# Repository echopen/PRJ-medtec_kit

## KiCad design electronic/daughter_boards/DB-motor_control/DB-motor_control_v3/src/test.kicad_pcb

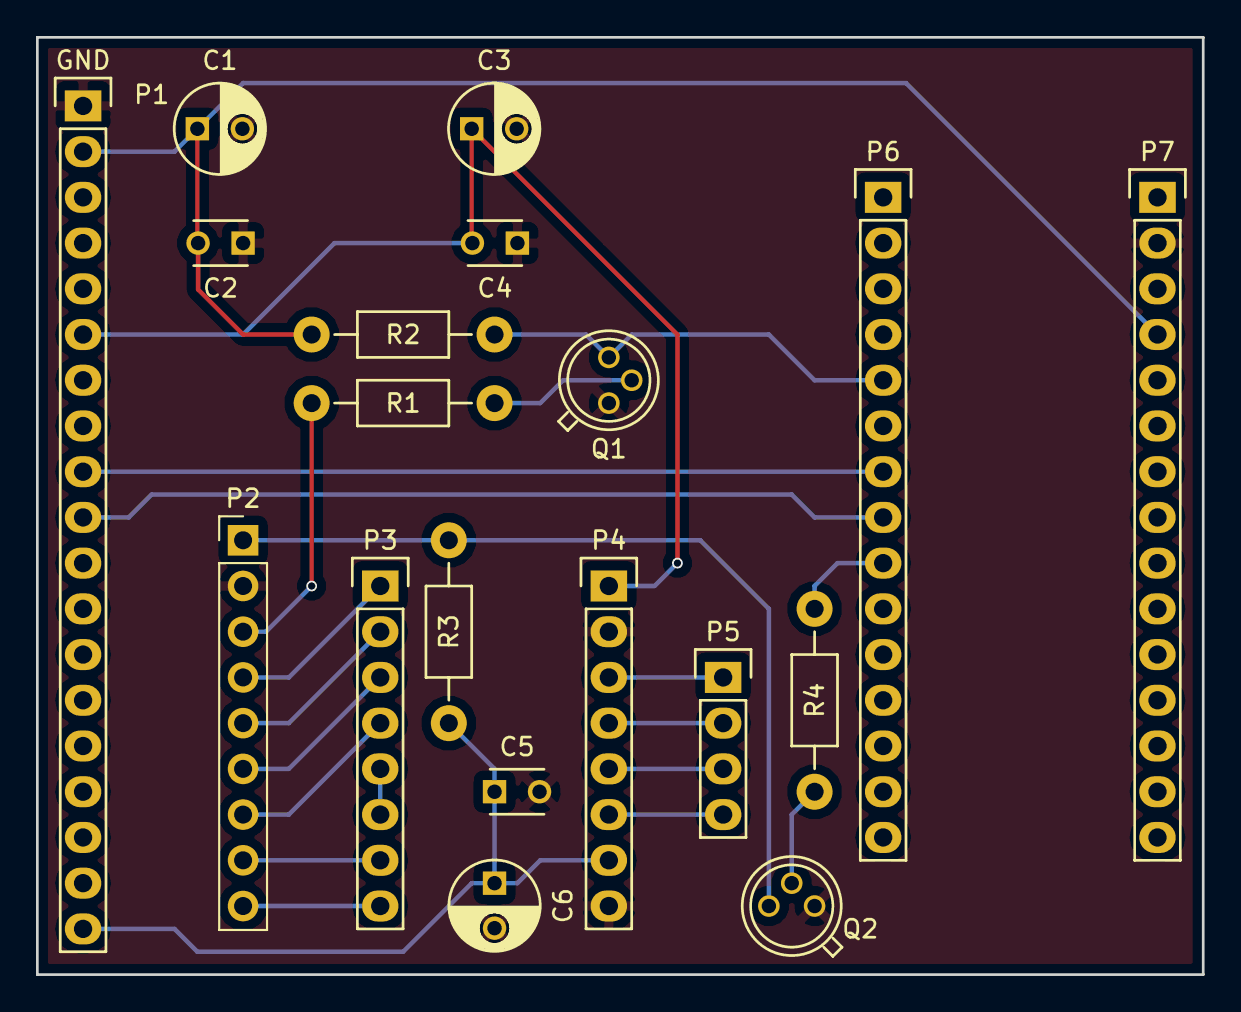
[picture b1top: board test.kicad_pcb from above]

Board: 2 copper layers, 64.8 x 52.1 mm, 19 parts (0 on the bottom side), 23 nets.

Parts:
C1, C6: 10u; CP_small_TH_echopen
C2, C4: 100n; C_small_TH_echopen
C3: 100u; CP_small_TH_echopen
C5: 47n; C_small_TH_echopen
P1: CONN_01X19; Header_pin_angled_1x19
P2: CONN_01X09; Socket_Strip_Straight_1x09_Pitch2.54mm
P3, P4: CONN_01X08; Pin_Header_Straight_1x08
P5: CONN_01X04; Pin_Header_Straight_1x04
P6: CONN_01X15; Socket_Strip_Straight_1x15
P7: CONN_01X15; Pin_Header_Straight_1x15
Q1, Q2: 2N2222; TO-18_TH_common
R1, R4: 680; Resistor_TH_common
R2, R3: 1.5k; Resistor_TH_common

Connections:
GND: C1.2, C2.1, C3.2, C4.1, C5.2, C6.2, P1.1, P2.2, P4.2, P4.8, P7.2, Q1.1, Q2.1
unnamed: C1.1, C2.2, P1.2, P7.4, R2.2
unnamed: C3.1, C4.2, P1.6, P4.1
unnamed: C5.1, C6.1, P1.19, P4.7, R3.2
unnamed: P1.9, P6.7
unnamed: P1.10, P6.8
unnamed: P2.1, Q2.3, R3.1
unnamed: P2.3, R1.2
unnamed: P2.4, P3.1
unnamed: P2.5, P3.2
unnamed: P2.6, P3.3
unnamed: P2.7, P3.4
unnamed: P2.8, P3.7
unnamed: P2.9, P3.8
unnamed: P3.5, P3.6
unnamed: P4.3, P5.1
unnamed: P4.4, P5.2
unnamed: P4.5, P5.3
unnamed: P4.6, P5.4
unnamed: P6.5, Q1.3, R2.1
unnamed: P6.9, R4.1
unnamed: Q1.2, R1.1
unnamed: Q2.2, R4.2

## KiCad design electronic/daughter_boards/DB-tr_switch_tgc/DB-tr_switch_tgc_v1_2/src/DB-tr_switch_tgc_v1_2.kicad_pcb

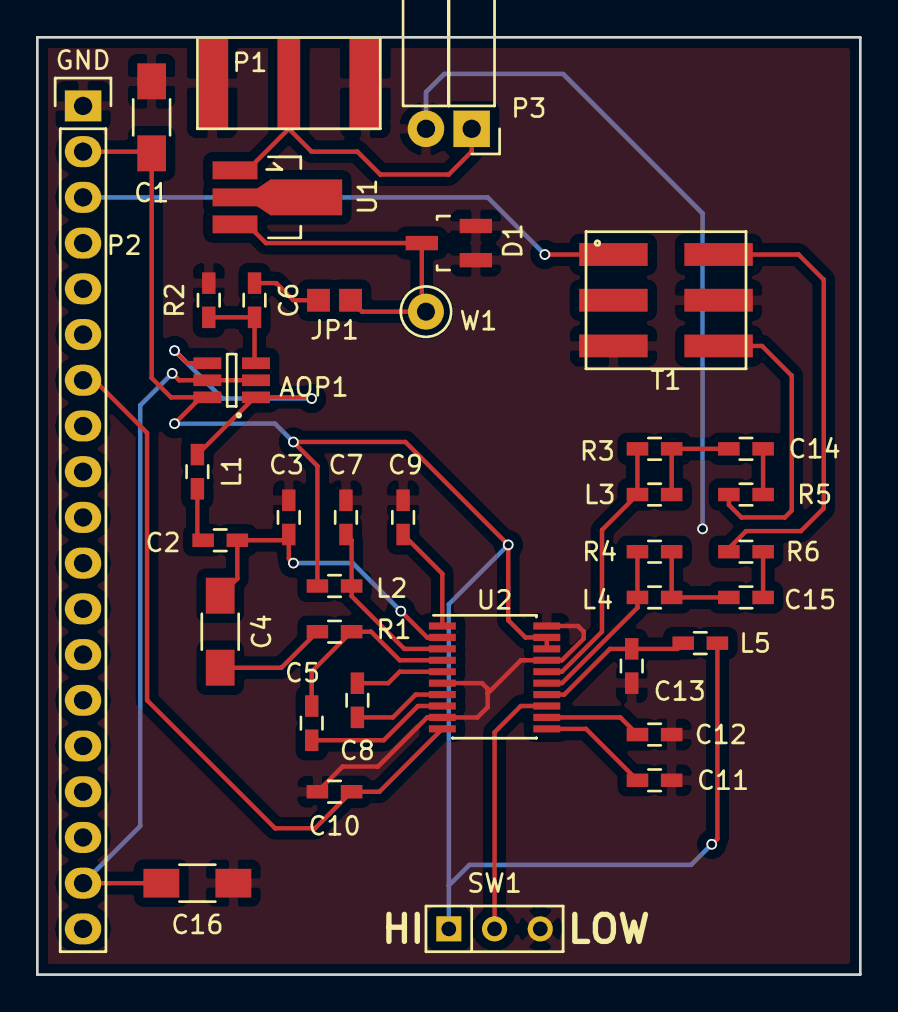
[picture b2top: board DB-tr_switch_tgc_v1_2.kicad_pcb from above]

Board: 2 copper layers, 45.7 x 52.1 mm, 38 parts (0 on the bottom side), 31 nets.

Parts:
AOP1: OPA625; SOT-23-6_Handsoldering(OPA625)
C1, C16: 10u; CMS_1206
C2, C5, C7, C8, C9, C11, C12, C13, C14, C15: 100n; CMS_0603
C3: 22p; CMS_0603
C4: 18n; CMS_1206
C6, C10: 1n; CMS_0603
D1: BAV99; SOT-23
JP1: JUMPER; Jumper
L1, L2, L3, L4, L5: 120n; CMS_0603
P1: SMA
P2: CONN_01X19; Header_pin_angled_1x19
P3: CONN_01X02; Socket_Strip_Angled_1x02
R1: 274; CMS_0603
R2: 220; CMS_0603
R3, R4: 100; CMS_0603
R5, R6: 237; CMS_0603
SW1: SWITCH_INV; SW_Micro_SPST
T1: TRANSFO_6pins; Transfo_6pins(coilcraft)
U1: MD0100; SOT89-3_(MD0100)
U2: AD8331; QSOP-20(AD8331)
W1: TEST_1P; Test_Point_Keystone_5000-5004_Miniature

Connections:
GND: C1.2, C3.1, C7.1, C9.1, C10.2, C11.2, C12.2, C13.2, C16.1, D1.2, D1.3, P1.2, P2.1, P3.2, R2.2, SW1.3, T1.2, T1.4, U2.6, U2.9, U2.17, U2.20
unnamed: AOP1.1, AOP1.4, L1.1
unnamed: AOP1.2, AOP1.5, C16.2, P2.18
unnamed: AOP1.3, C6.2, R2.1
unnamed: AOP1.6, C1.1, L2.1, L5.2, P2.2, SW1.1, U2.18, U2.19
unnamed: C2.1, L1.2
unnamed: C2.2, C3.2, C4.1, U2.2
unnamed: C4.2, R1.1
unnamed: C5.1, R1.2, U2.4
unnamed: C5.2, U2.8
unnamed: C6.1, JP1.2
unnamed: C7.2, L2.2, U2.3
unnamed: C8.1, U2.5
unnamed: C8.2, U2.7
unnamed: C9.2, U2.1
unnamed: C10.1, P2.7, U2.10
unnamed: C11.1, U2.11
unnamed: C12.1, U2.12
unnamed: C13.1, L5.1, U2.14
unnamed: C14.1, R5.2
unnamed: C14.2, L3.2, R3.1
unnamed: C15.1, R6.2
unnamed: C15.2, L4.2, R4.1
unnamed: D1.1, JP1.1, U1.3, W1.1
unnamed: L3.1, R3.2, U2.16
unnamed: L4.1, R4.2, U2.15
unnamed: P1.1, P3.1, U1.1
unnamed: P2.3, T1.6
unnamed: R5.1, T1.3
unnamed: R6.1, T1.1
unnamed: SW1.2, U2.13

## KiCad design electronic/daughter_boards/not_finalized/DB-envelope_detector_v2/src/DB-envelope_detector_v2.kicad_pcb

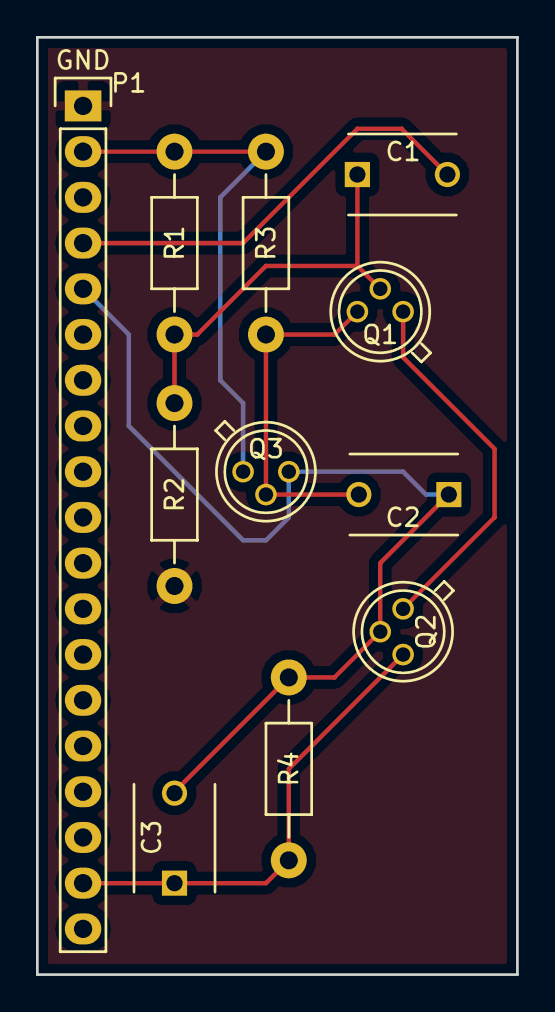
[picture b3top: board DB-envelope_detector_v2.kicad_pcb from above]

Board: 2 copper layers, 26.7 x 52.1 mm, 11 parts (0 on the bottom side), 8 nets.

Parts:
C1: 10nF; C_Disc_D6_P5
C2: 1nF; C_Disc_D6_P5
C3: 33nF; C_Disc_D6_P5
P1: CONN_01X19; Header_pin_angled_1x19
Q1: 2N2222; TO-18_3Pin
Q2, Q3: 2N2907; TO-18_3Pin
R1: 2800; Resistor_Horizontal_RM10mm
R2: 1000; Resistor_Horizontal_RM10mm
R3, R4: 330; Resistor_Horizontal_RM10mm

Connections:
GND: P1.1, R2.2
unnamed: C1.1, Q1.2, R1.2, R2.1
unnamed: C1.2, P1.4
unnamed: C2.1, C3.2, P1.5, Q2.2, Q3.3, R4.1
unnamed: C2.2, Q1.3, Q3.2, R3.2
unnamed: C3.1, P1.18, Q2.3, R4.2
unnamed: P1.2, Q3.1, R1.1, R3.1
unnamed: Q1.1, Q2.1
